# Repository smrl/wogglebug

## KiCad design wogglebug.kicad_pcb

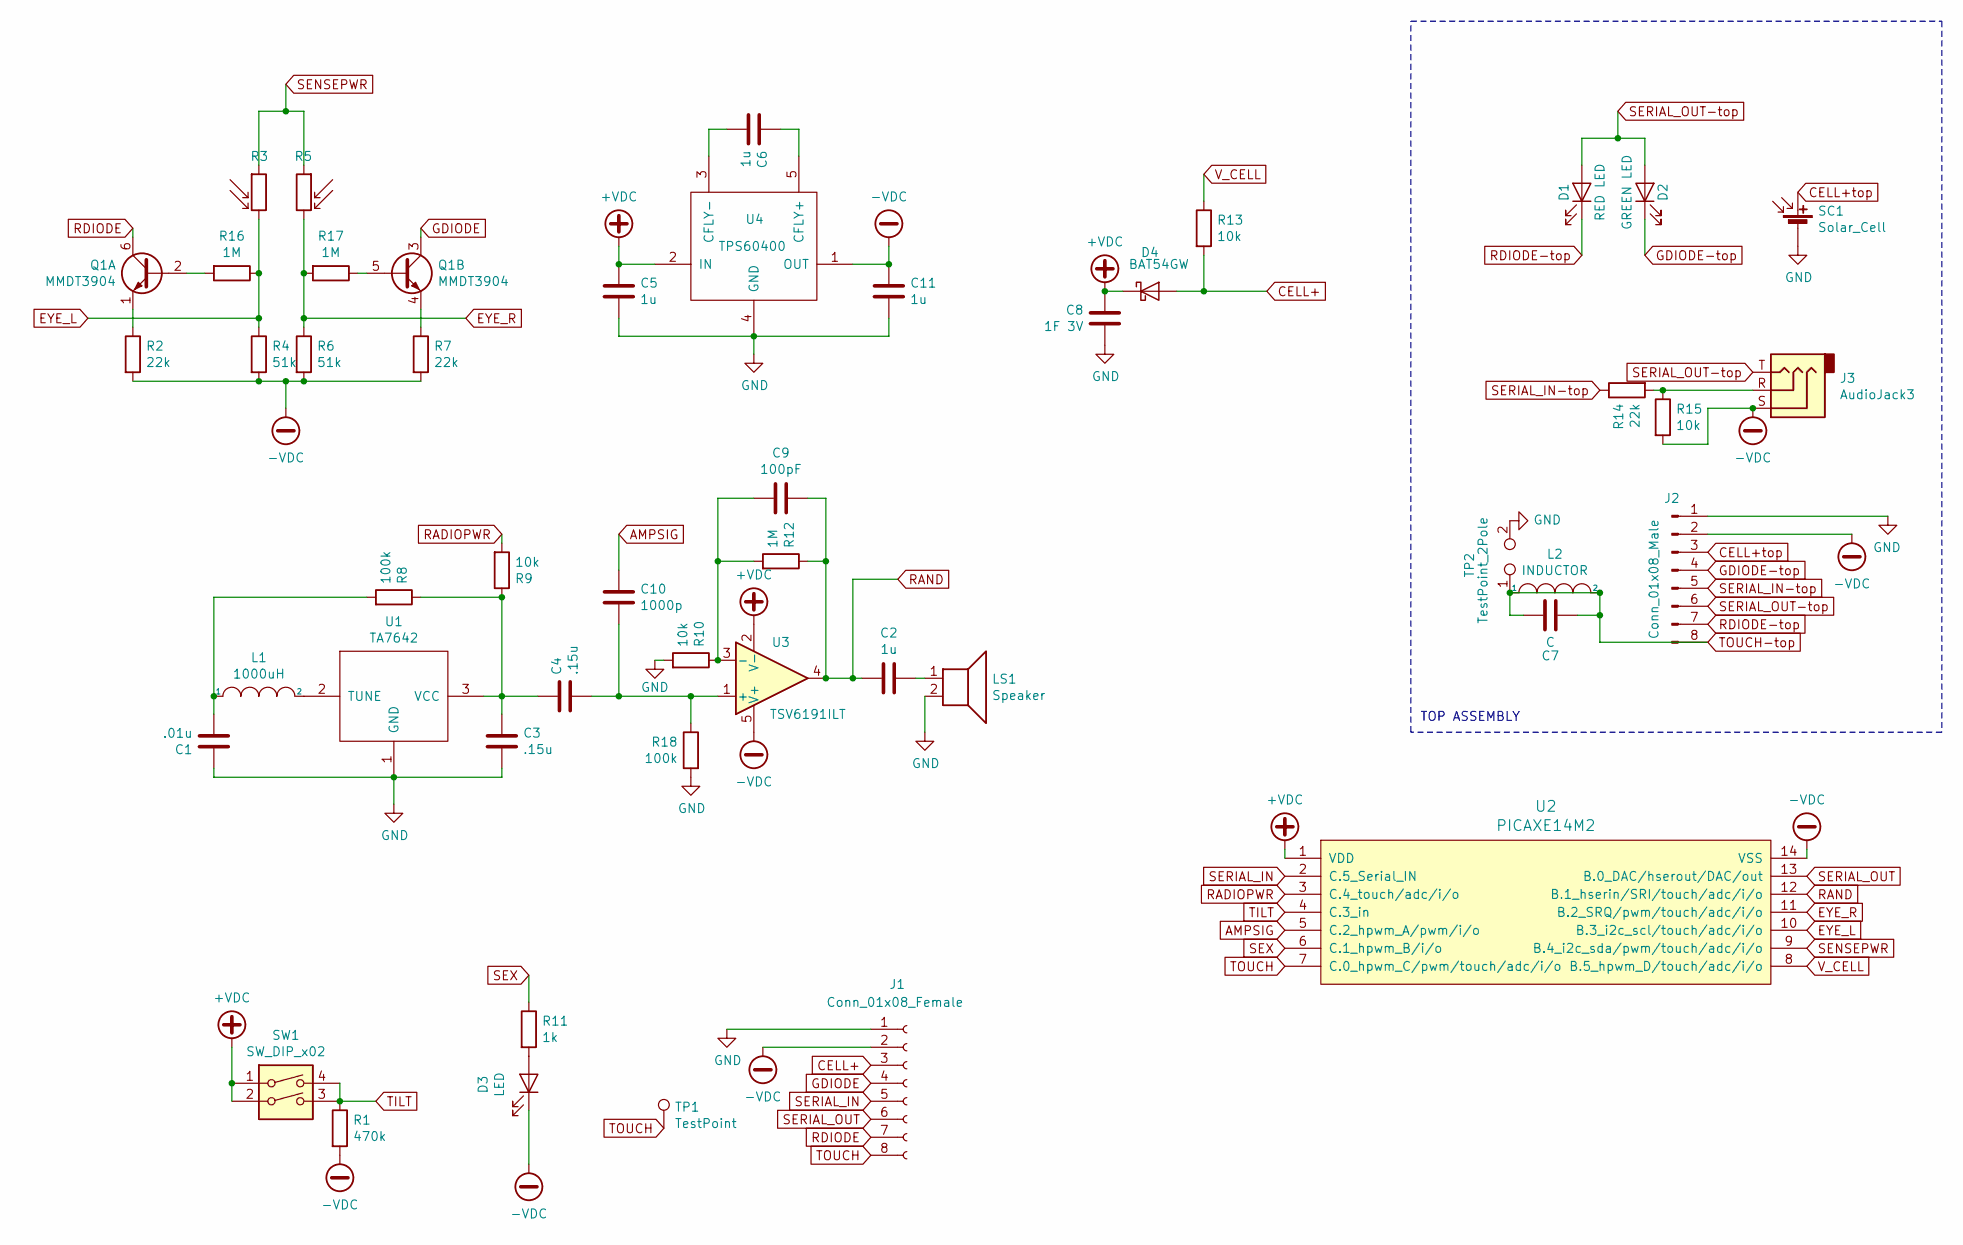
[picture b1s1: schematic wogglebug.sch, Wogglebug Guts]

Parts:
C1: .01u; C_0603_1608Metric
C2, C5, C6, C11: 1u; C_0603_1608Metric
C3, C4: .15u; C_0603_1608Metric
C7: C; C_0603_1608Metric
C8: 1F 3V; supercap
C9: 100pF; C_0603_1608Metric
C10: 1000p; C_0603_1608Metric
D1: RED LED; LED_0805_2012Metric
D2: GREEN LED; LED_0805_2012Metric
D3: LED; LED_D5.0mm_Horizontal_O1.27mm_Z3.0mm_Clear
D4: BAT54GW; D_SOD-123
J1: Conn_01x08_Female; PinSocket_1x08_P2.54mm_Vertical
J2: Conn_01x08_Male; PinHeader_1x08_P2.54mm_Vertical_SMD_Pin1Left
J3: AudioJack3; Jack_3.5mm_CUI_SJ-3523-SMT_Horizontal
L1: 1000uH; L_1206_3216Metric
L2: INDUCTOR; board_inductor
LS1: Speaker; MagBuzzer
Q1: MMDT3904; SOT-363_SC-70-6
R1: 470k; R_0603_1608Metric
R2, R7, R14: 22k; R_0603_1608Metric
R3, R5: PinHeader_1x02_P2.00mm_Vertical
R4, R6: 51k; R_0603_1608Metric
R8, R18: 100k; R_0603_1608Metric
R9, R10, R13, R15: 10k; R_0603_1608Metric
R11: 1k; R_0603_1608Metric
R12, R16, R17: 1M; R_0603_1608Metric
SC1: Solar_Cell; Solar Cell 3.3V 20x40mm
SW1: SW_DIP_x02; tiltswitch
TP1: TestPoint; PinHeader_1x01_P2.54mm_Vertical
TP2: TestPoint_2Pole; SolderJumper-2_P1.3mm_Open_TrianglePad1.0x1.5mm
U1: TA7642; TO-92
U2: PICAXE14M2; SOIC-14_3.9x8.7mm_P1.27mm
U3: TSV6191ILT; SOT-23-5
U4: TPS60400; SOT-23-5

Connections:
+VDC: C5.1, C8.1, D4.1 (K), SW1.1, SW1.2, U2.1 (VDD), U3.2 (V-), U4.2 (IN)
-VDC: C11.1, D3.1 (K), J1.2, J2.2, J3.S, R1.2, R2.2, R4.2, R6.2, R7.2, R15.2, U2.14 (VSS), U3.5 (V+), U4.1 (OUT)
AMPSIG: C10.1, U2.5 (C.2_hpwm_A/pwm/i/o)
CELL+: D4.2 (A), J1.3, R13.2
CELL+top: J2.3, SC1.1 (+)
EYE_L: R3.2, R4.1, R16.1, U2.10 (B.3_i2c_scl/touch/adc/i/o)
EYE_R: R5.2, R6.1, R17.2, U2.11 (B.2_SRQ/pwm/touch/adc/i/o)
GDIODE: J1.4, Q1.3 (C2)
GDIODE-top: D2.1 (K), J2.4
GND: C1.1, C3.2, C5.2, C8.2, C11.2, J1.1, J2.1, LS1.2, R10.2, R18.2, SC1.2 (-), TP2.2, U1.1 (GND), U4.4 (GND)
unnamed: C1.2, L1.1, R8.2
unnamed: C2.1, LS1.1
unnamed: C3.1, C4.1, R8.1, R9.1, U1.3 (VCC)
unnamed: C6.1, U4.5 (CFLY+)
unnamed: C6.2, U4.3 (CFLY-)
unnamed: C9.2, R10.1, R12.2, U3.3 (-)
unnamed: C4.2, C10.2, R18.1, U3.1 (+)
unnamed: D3.2 (A), R11.2
unnamed: J3.R, R14.2, R15.1
unnamed: L1.2, U1.2 (TUNE)
unnamed: Q1.1 (E1), R2.1
unnamed: Q1.2 (B1), R16.2
unnamed: Q1.4 (E2), R7.1
unnamed: Q1.5 (B2), R17.1
RADIOPWR: R9.2, U2.3 (C.4_touch/adc/i/o)
RAND: C2.2, C9.1, R12.1, U2.12 (B.1_hserin/SRI/touch/adc/i/o), U3.4
RDIODE: J1.7, Q1.6 (C1)
RDIODE-top: D1.1 (K), J2.7
SENSEPWR: R3.1, R5.1, U2.9 (B.4_i2c_sda/pwm/touch/adc/i/o)
SERIAL_IN: J1.5, U2.2 (C.5_Serial_IN)
SERIAL_IN-top: J2.5, R14.1
SERIAL_OUT: J1.6, U2.13 (B.0_DAC/hserout/DAC/out)
SERIAL_OUT-top: D1.2 (A), D2.2 (A), J2.6, J3.T
SEX: R11.1, U2.6 (C.1_hpwm_B/i/o)
TILT: R1.1, SW1.3, SW1.4, U2.4 (C.3_in)
TOUCH: J1.8, TP1.1, U2.7 (C.0_hpwm_C/pwm/touch/adc/i/o)
TOUCH-top: C7.1, C7.2, J2.8, L2.1, L2.2, TP2.1
V_CELL: R13.1, U2.8 (B.5_hpwm_D/touch/adc/i/o)

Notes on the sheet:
TOP ASSEMBLY

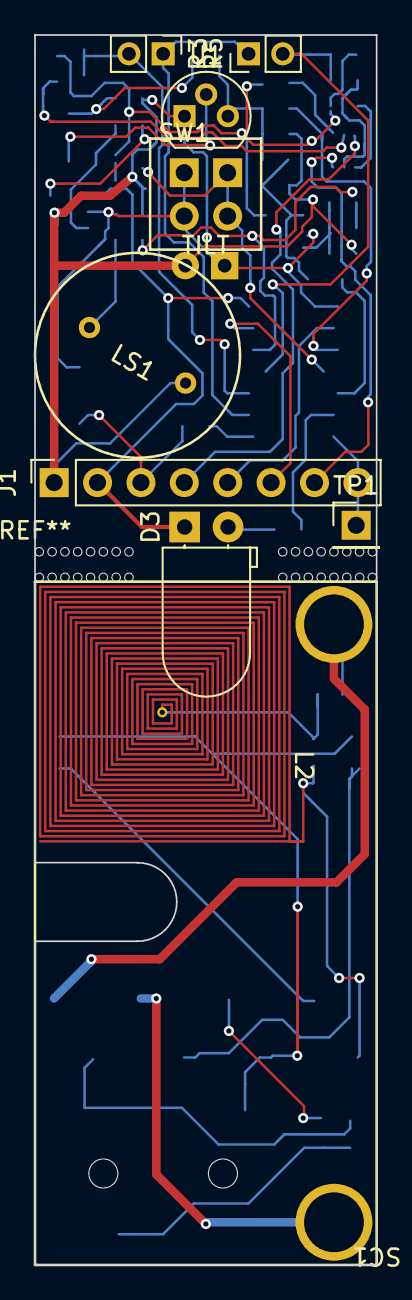
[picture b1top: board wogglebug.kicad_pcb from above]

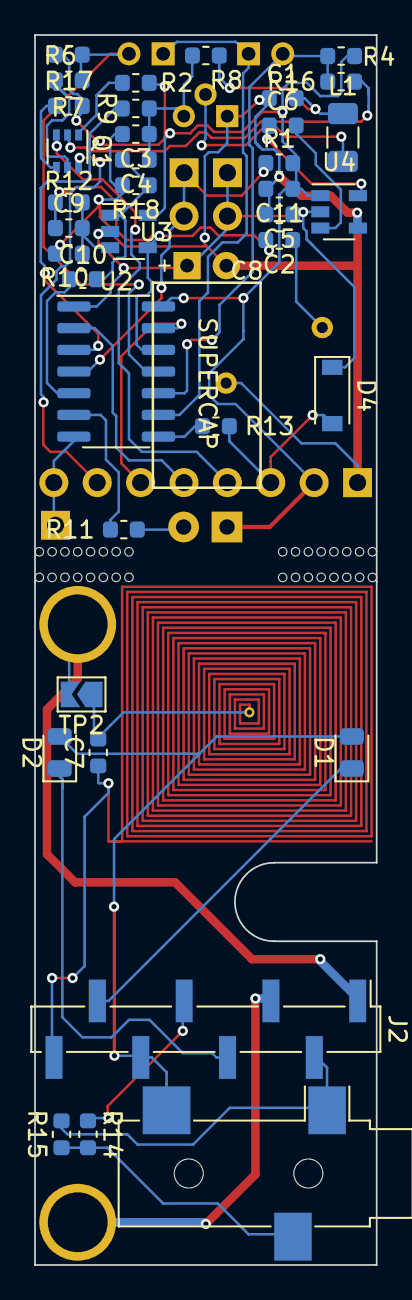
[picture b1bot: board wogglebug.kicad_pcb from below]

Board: 2 copper layers, 20.0 x 72.0 mm, 48 parts (38 on the bottom side), 38 nets.
